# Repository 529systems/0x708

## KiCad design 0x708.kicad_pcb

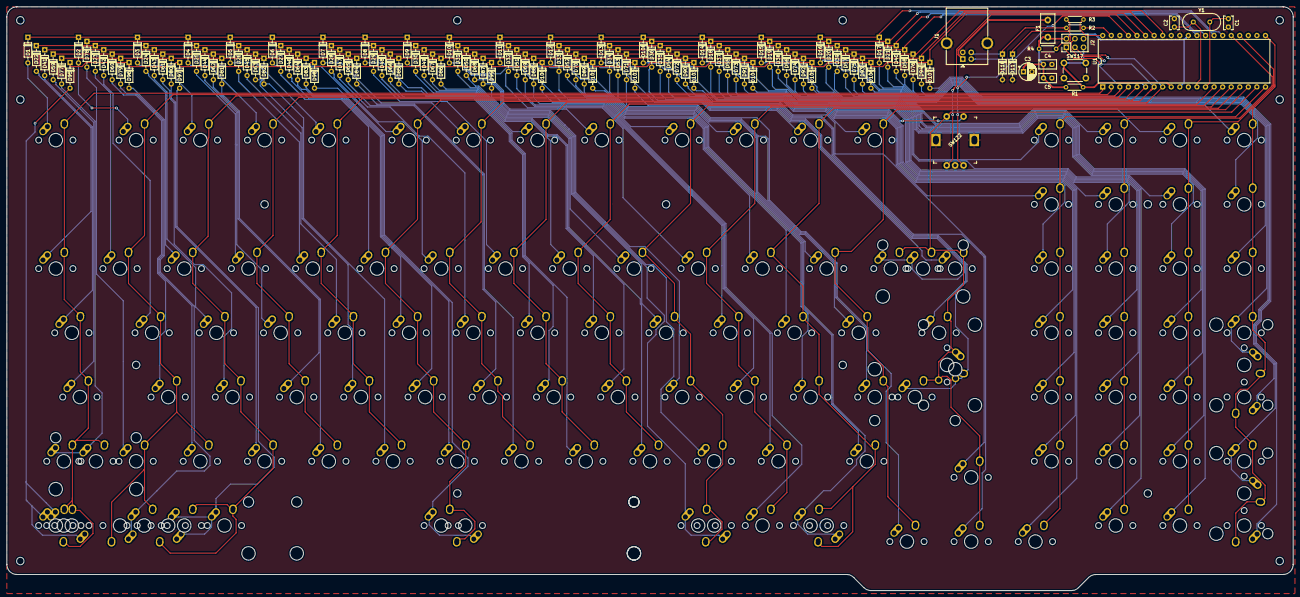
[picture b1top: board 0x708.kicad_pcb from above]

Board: 2 copper layers, 381.5 x 173.1 mm, 261 parts (0 on the bottom side), 145 nets.

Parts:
C1, C2: 20p; C_Disc_D3.8mm_W2.6mm_P2.50mm
C3: 4.7u; CP_Radial_D5.0mm_P2.50mm
C4, C5: 100n; C_Disc_D5.0mm_W2.5mm_P2.50mm
D1, D2, D3, D4, D5, D6, D7, D8, D9, D10, D11, D12, D13, D14, D15, D16, D17, D18, D19, D20, D21, D22, D23, D24, D25, D26, D27, D28, D29, D30, D31, D32, D33, D34, D35, D36, D37, D38, D39, D40, D41, D42, D43, D44, D45, D46, D47, D48, D49, D50, D51, D52, D53, D54, D55, D56, D57, D58, D59, D60, D61, D62, D63, D64, D65, D66, D67, D68, D69, D70, D71, D72, D73, D74, D75, D76, D77, D78, D79, D80, D81, D82, D83, D84, D85, D86, D87, D88, D89, D90, D91, D92, D93, D94, D95, D96, D97, D98, D99, D100, D101, D102, D103, D104, D105, D106, D107, D108: D_Small; D_DO-35_SOD27_P7.62mm_Horizontal
D117, D118: 3.6V; D_DO-35_SOD27_P7.62mm_Horizontal
F1: 100mA; Fuse_Littelfuse_395Series
H1, H2, H3, H4, H5, H6, H7, H8, H9, H10, H11, H12, H13, H14, H15: M2; MountingHole_2.2mm_M2
J1: USB_B; USB_B_OST_USB-B1HSxx_Horizontal
J2: AVR-ISP-6; PinHeader_2x03_P2.54mm_Vertical
R1: 10k; R_Axial_DIN0204_L3.6mm_D1.6mm_P5.08mm_Horizontal
R2, R3: 75; R_Axial_DIN0204_L3.6mm_D1.6mm_P5.08mm_Horizontal
R4: 1.5k; R_Axial_DIN0204_L3.6mm_D1.6mm_P5.08mm_Horizontal
SW1: Esc; MX-1U-NoLED
SW2: F1; MX-1U-NoLED
SW3: F2; MX-1U-NoLED
SW4: F3; MX-1U-NoLED
SW5: F4; MX-1U-NoLED
SW6: F5; MX-1U-NoLED
SW7: F6; MX-1U-NoLED
SW8: F7; MX-1U-NoLED
SW9: F8; MX-1U-NoLED
SW10: F9; MX-1U-NoLED
SW11: F10; MX-1U-NoLED
SW12: F11; MX-1U-NoLED
SW13: F12; MX-1U-NoLED
SW14: Ins; MX-1U-NoLED
SW15: Home; MX-1U-NoLED
SW16: PgUp; MX-1U-NoLED
SW17: PrtSc; MX-1U-NoLED
SW18: Del; MX-1U-NoLED
SW19: End; MX-1U-NoLED
SW20: PgDn; MX-1U-NoLED
SW21: ScrLk; MX-1U-NoLED
SW22: `; MX-1U-NoLED
SW23: 1; MX-1U-NoLED
SW24: 2; MX-1U-NoLED
SW25: 3; MX-1U-NoLED
SW26: 4; MX-1U-NoLED
SW27: 5; MX-1U-NoLED
SW28: 6; MX-1U-NoLED
SW29: 7; MX-1U-NoLED
SW30: 8; MX-1U-NoLED
SW31: 9; MX-1U-NoLED
SW32: 0; MX-1U-NoLED
SW33: -; MX-1U-NoLED
SW34: =; MX-1U-NoLED
SW35: Backspace; MX-2U-NoLED
SW36: Backspace2; MX-1U-NoLED
SW37: NumLk; MX-1U-NoLED
SW38: Num/; MX-1U-NoLED
SW39: Num*; MX-1U-NoLED
SW40: Num-; MX-1U-NoLED
SW41: Tab; MX-1.5U-NoLED
SW42: Q; MX-1U-NoLED
SW43: W; MX-1U-NoLED
SW44: E; MX-1U-NoLED
SW45: R; MX-1U-NoLED
SW46: T; MX-1U-NoLED
SW47: Y; MX-1U-NoLED
SW48: U; MX-1U-NoLED
SW49: I; MX-1U-NoLED
SW50: O; MX-1U-NoLED
SW51: P; MX-1U-NoLED
SW52: [; MX-1U-NoLED
SW53: ]; MX-1U-NoLED
SW54: \; MX-1.5U-NoLED
SW55: Num7; MX-1U-NoLED
SW56: Num8; MX-1U-NoLED
SW57: Num9; MX-1U-NoLED
SW58: Num+; MX-2U-NoLED
SW59: ALk; MX-1.75U-NoLED
SW60: A; MX-1U-NoLED
SW61: S; MX-1U-NoLED
SW62: D; MX-1U-NoLED
SW63: F; MX-1U-NoLED
SW64: G; MX-1U-NoLED
SW65: H; MX-1U-NoLED
SW66: J; MX-1U-NoLED
SW67: K; MX-1U-NoLED
SW68: L; MX-1U-NoLED
SW69: ;; MX-1U-NoLED
SW70: '; MX-1U-NoLED
SW71: ISO#; MX-1U-NoLED
SW72: Enter; MX-2.25U-ReversedStabilizers-NoLED
SW73: Num4; MX-1U-NoLED
SW74: Num5; MX-1U-NoLED
SW75: Num6; MX-1U-NoLED
SW76: Num+2; MX-1U-NoLED
SW77: LShift; MX-2.25U-NoLED
SW78: ISO\; MX-1U-NoLED
SW79: Z; MX-1U-NoLED
SW80: X; MX-1U-NoLED
SW81: C; MX-1U-NoLED
SW82: V; MX-1U-NoLED
SW83: B; MX-1U-NoLED
SW84: N; MX-1U-NoLED
SW85: M; MX-1U-NoLED
SW86: ,; MX-1U-NoLED
SW87: .; MX-1U-NoLED
SW88: /; MX-1U-NoLED
SW89: RShift; MX-1.75U-NoLED
SW90: Up; MX-1U-NoLED
SW91: Num1; MX-1U-NoLED
SW92: Num2; MX-1U-NoLED
SW93: Num3; MX-1U-NoLED
SW94: NumEnter; MX-2U-NoLED
SW95: LCtrl; MX-1U-NoLED
SW96: LWin; MX-1U-NoLED
SW97: LAlt; MX-1U-NoLED
SW98: Space; MX-7U-NoLED
SW99: RAlt; MX-1U-NoLED
SW100: RWin; MX-1U-NoLED
SW101: RCtrl; MX-1U-NoLED
SW102: Left; MX-1U-NoLED
SW103: Down; MX-1U-NoLED
SW104: Right; MX-1U-NoLED
SW105: Num0; MX-1U-NoLED
SW106: Num.; MX-1U-NoLED
SW107: NumEnter2; MX-1U-NoLED
SW108: LShift2; MX-1.25U-NoLED
SW109: Backspace1; MX-1U-NoLED
SW110: ISOEnter; MX-ISO-NoLED
SW111: Num+1; MX-1U-NoLED
SW112: LCtrl1.25; MX-1.25U-NoLED
SW113: LWin1.25; MX-1.25U-NoLED
SW114: LAlt1.25; MX-1.25U-NoLED
SW115: Space6.25; MX-6.25U-ReversedStabilizers-NoLED
SW116: NumEnter1; MX-1U-NoLED
SW117: RESET; SW_PUSH_6mm
SW118: LCtrl1.5; MX-1.5U-NoLED
SW119: LAlt1.5; MX-1.5U-NoLED
SW120: RAlt1.5; MX-1.5U-NoLED
SW121: RCtrl1.5; MX-1.5U-NoLED
SW122: Rotary_Encoder_Switch; Rotary_Encoder_Switched_PEC11R
U1: ATmega32A-PU; DIP-40_W15.24mm
Y1: 16MHz; Crystal_HC49-U_Vertical

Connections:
+5V: C3.1, C4.1, C5.1, F1.1, J2.2, R1.1, R4.2, U1.10, U1.30
COL1: SW1.2, SW22.2, SW41.2, SW59.2, SW77.2, SW95.2, SW108.2, SW112.2, SW118.2, U1.1
COL2: SW2.2, SW23.2, SW42.2, SW60.2, SW78.2, SW79.2, SW96.2, SW113.2, U1.2
COL3: SW3.2, SW24.2, SW43.2, SW61.2, SW80.2, SW97.2, SW114.2, SW119.2, U1.3
COL4: SW4.2, SW25.2, SW44.2, SW62.2, SW81.2, U1.4
COL5: SW5.2, SW26.2, SW45.2, SW63.2, SW82.2, U1.5
COL6: J2.4, SW6.2, SW27.2, SW46.2, SW64.2, SW83.2, SW98.2, SW115.2, U1.6
COL7: J2.1, SW7.2, SW28.2, SW47.2, SW65.2, SW84.2, U1.7
COL8: J2.3, SW8.2, SW29.2, SW48.2, SW66.2, SW85.2, U1.8
COL9: SW9.2, SW30.2, SW49.2, SW67.2, SW86.2, U1.14
COL10: SW10.2, SW31.2, SW50.2, SW68.2, SW87.2, SW99.2, SW120.2, U1.15
COL11: SW11.2, SW32.2, SW51.2, SW69.2, SW88.2, SW100.2, U1.16
COL12: SW12.2, SW33.2, SW52.2, SW70.2, SW89.2, SW101.2, SW121.2, U1.17
COL13: SW13.2, SW34.2, SW53.2, SW71.2, SW102.2, U1.18
COL14: SW35.2, SW36.2, SW54.2, SW72.2, SW90.2, SW103.2, SW109.2, SW110.2, SW122.1, U1.19
COL15: SW14.2, SW18.2, SW37.2, SW55.2, SW73.2, SW91.2, SW104.2, U1.20
COL16: SW15.2, SW19.2, SW38.2, SW56.2, SW74.2, SW92.2, SW105.2, U1.25
COL17: SW16.2, SW20.2, SW39.2, SW57.2, SW75.2, SW93.2, SW106.2, U1.24
COL18: SW17.2, SW21.2, SW40.2, SW58.2, SW76.2, SW94.2, SW107.2, SW111.2, SW116.2, U1.21
D+: R2.1, U1.39
D-: R3.1, U1.40
GND: C1.2, C2.2, C3.2, C4.2, C5.2, D117.2, D118.2, J1.4, J1.5, J2.6, SW117.2, SW122.3, SW122.C, U1.11, U1.31
unnamed: D1.2, SW1.1
unnamed: D2.2, SW2.1
unnamed: D3.2, SW3.1
unnamed: D4.2, SW4.1
unnamed: D5.2, SW5.1
unnamed: D6.2, SW6.1
unnamed: D7.2, SW7.1
unnamed: D8.2, SW8.1
unnamed: D9.2, SW9.1
unnamed: D10.2, SW10.1
unnamed: D11.2, SW11.1
unnamed: D12.2, SW12.1
unnamed: D13.2, SW13.1
unnamed: D14.2, SW14.1
unnamed: D15.2, SW15.1
unnamed: D16.2, SW16.1
unnamed: D17.2, SW17.1
unnamed: D18.2, SW18.1
unnamed: D19.2, SW19.1
unnamed: D20.2, SW20.1
unnamed: D21.2, SW21.1
unnamed: D22.2, SW22.1
unnamed: D23.2, SW23.1
unnamed: D24.2, SW24.1
unnamed: D25.2, SW25.1
unnamed: D26.2, SW26.1
unnamed: D27.2, SW27.1
unnamed: D28.2, SW28.1
unnamed: D29.2, SW29.1
unnamed: D30.2, SW30.1
unnamed: D31.2, SW31.1
unnamed: D32.2, SW32.1
unnamed: D33.2, SW33.1
unnamed: D34.2, SW34.1
unnamed: D35.2, SW35.1, SW109.1
unnamed: D36.2, SW36.1
unnamed: D37.2, SW37.1
unnamed: D38.2, SW38.1
unnamed: D39.2, SW39.1
unnamed: D40.2, SW40.1
unnamed: D41.2, SW41.1
unnamed: D42.2, SW42.1
unnamed: D43.2, SW43.1
unnamed: D44.2, SW44.1
unnamed: D45.2, SW45.1
unnamed: D46.2, SW46.1
unnamed: D47.2, SW47.1
unnamed: D48.2, SW48.1
unnamed: D49.2, SW49.1
unnamed: D50.2, SW50.1
unnamed: D51.2, SW51.1
unnamed: D52.2, SW52.1
unnamed: D53.2, SW53.1
unnamed: D54.2, SW54.1
unnamed: D55.2, SW55.1
unnamed: D56.2, SW56.1
unnamed: D57.2, SW57.1
unnamed: D58.2, SW58.1, SW111.1
unnamed: D59.2, SW59.1
unnamed: D60.2, SW60.1
unnamed: D61.2, SW61.1
unnamed: D62.2, SW62.1
unnamed: D63.2, SW63.1
unnamed: D64.2, SW64.1
unnamed: D65.2, SW65.1
unnamed: D66.2, SW66.1
unnamed: D67.2, SW67.1
unnamed: D68.2, SW68.1
unnamed: D69.2, SW69.1
unnamed: D70.2, SW70.1
unnamed: D71.2, SW71.1
unnamed: D72.2, SW72.1, SW110.1
unnamed: D73.2, SW73.1
unnamed: D74.2, SW74.1
unnamed: D75.2, SW75.1
unnamed: D76.2, SW76.1
unnamed: D77.2, SW77.1, SW108.1
unnamed: D78.2, SW78.1
unnamed: D79.2, SW79.1
unnamed: D80.2, SW80.1
unnamed: D81.2, SW81.1
unnamed: D82.2, SW82.1
unnamed: D83.2, SW83.1
unnamed: D84.2, SW84.1
unnamed: D85.2, SW85.1
unnamed: D86.2, SW86.1
unnamed: D87.2, SW87.1
unnamed: D88.2, SW88.1
unnamed: D89.2, SW89.1
unnamed: D90.2, SW90.1
unnamed: D91.2, SW91.1
unnamed: D92.2, SW92.1
unnamed: D93.2, SW93.1
unnamed: D94.2, SW94.1, SW116.1
unnamed: D95.2, SW95.1, SW112.1, SW118.1
unnamed: D96.2, SW96.1, SW113.1
unnamed: D97.2, SW97.1, SW114.1, SW119.1
unnamed: D98.2, SW98.1, SW115.1
unnamed: D99.2, SW99.1, SW120.1
unnamed: D100.2, SW100.1
unnamed: D101.2, SW101.1, SW121.1
unnamed: D102.2, SW102.1
unnamed: D103.2, SW103.1
unnamed: D104.2, SW104.1
unnamed: D105.2, SW105.1
unnamed: D106.2, SW106.1
unnamed: D107.2, SW107.1
unnamed: D117.1, J1.2, R3.2, R4.1
unnamed: D118.1, J1.3, R2.2
unnamed: F1.2, J1.1
RESET: J2.5, R1.2, SW117.1, U1.9
ROTA: SW122.A, U1.36
ROTB: SW122.B, U1.37
ROTS2: D108.2, SW122.2
ROWA: D1.1, D2.1, D3.1, D4.1, D5.1, D6.1, D7.1, D8.1, D9.1, D10.1, D11.1, D12.1, D13.1, D14.1, D15.1, D16.1, D17.1, D108.1, U1.26
ROWB: D18.1, D19.1, D20.1, D21.1, D36.1, D78.1, U1.27
ROWC: D22.1, D23.1, D24.1, D25.1, D26.1, D27.1, D28.1, D29.1, D30.1, D31.1, D32.1, D33.1, D34.1, D35.1, D37.1, D38.1, D39.1, D40.1, U1.28
ROWD: D41.1, D42.1, D43.1, D44.1, D45.1, D46.1, D47.1, D48.1, D49.1, D50.1, D51.1, D52.1, D53.1, D54.1, D55.1, D56.1, D57.1, D58.1, U1.29
ROWE: D59.1, D60.1, D61.1, D62.1, D63.1, D64.1, D65.1, D66.1, D67.1, D68.1, D69.1, D70.1, D71.1, D72.1, D73.1, D74.1, D75.1, D76.1, U1.33
ROWF: D77.1, D79.1, D80.1, D81.1, D82.1, D83.1, D84.1, D85.1, D86.1, D87.1, D88.1, D89.1, D90.1, D91.1, D92.1, D93.1, D94.1, U1.34
ROWG: D95.1, D96.1, D97.1, D98.1, D99.1, D100.1, D101.1, D102.1, D103.1, D104.1, D105.1, D106.1, D107.1, U1.35
XTAL1: C1.1, U1.13, Y1.1
XTAL2: C2.1, U1.12, Y1.2

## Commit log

2019-08-09 new project
2019-08-14 rough draft
2019-08-14 ignore gerber files
2019-08-18 complete prototype
2019-08-18 add renders
2019-08-18 add bottom plate lasercut
